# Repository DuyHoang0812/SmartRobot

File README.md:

# SmartRobot

SmartRobot là hệ thống quản lý và điều khiển xe robot ESP32 qua web. Người dùng có thể xem trạng thái xe, nhận quyền điều khiển, lái bằng bàn phím hoặc D-Pad và chuyển sang chế độ tự tránh vật cản. Quản trị viên quản lý tài khoản, xe và thông tin xác thực của từng thiết bị.

Hệ thống gồm frontend React, backend FastAPI, PostgreSQL và firmware ESP-IDF. ESP32 kết nối Wi-Fi và chủ động trao đổi với backend qua HTTP(S); trình duyệt nhận trạng thái qua REST và WebSocket. Mỗi xe có thông tin xác thực riêng, hỗ trợ nhiều xe cùng hoạt động.

## Mục lục

- [Chức năng](#chức-năng)
- [Kiến trúc dự án](#kiến-trúc-dự-án)
- [Nguyên lý hoạt động](#nguyên-lý-hoạt-động)
- [Phần cứng và sơ đồ chân](#phần-cứng-và-sơ-đồ-chân)
- [Setup và chạy web](#setup-và-chạy-web)
- [Setup, build và nạp firmware](#setup-build-và-nạp-firmware)
- [Chạy toàn bộ hệ thống](#chạy-toàn-bộ-hệ-thống)
- [Kiểm thử và kiểm tra bản build](#kiểm-thử-và-kiểm-tra-bản-build)
- [Xử lý lỗi thường gặp](#xử-lý-lỗi-thường-gặp)
- [Tài liệu chi tiết](#tài-liệu-chi-tiết)

## Chức năng

| Đối tượng | Chức năng |
| --- | --- |
| Người dùng | Đăng nhập, xem danh sách và chi tiết xe, tìm/lọc xe Online–Offline–Busy |
| Người điều khiển | Nhận/Trả xe, điều khiển Tiến/Lùi/Trái/Phải, chọn Manual/Auto, theo dõi cảm biến và xác nhận lệnh |
| Quản trị viên | Tạo/sửa tài khoản, đổi quyền, kích hoạt/vô hiệu hóa, đặt lại mật khẩu; quản lý xe và xoay credential |
| ESP32 | Xác thực, heartbeat, lấy lệnh, gửi ACK và telemetry, điều khiển motor/servo/còi/relay, giám sát điều kiện dừng cục bộ |

Không có tài khoản mặc định hay đăng ký công khai. Admin đầu tiên được tạo bằng CLI; các tài khoản tiếp theo được tạo trên trang quản trị.

## Kiến trúc dự án

```mermaid
flowchart LR
    User[Người dùng] --> Web[React / Vite]
    Web -->|REST: đăng nhập, quản lý, điều khiển| API[FastAPI]
    API -->|WebSocket: trạng thái xe| Web
    API <-->|SQLAlchemy / psycopg| DB[(PostgreSQL)]
    ESP[ESP32 / ESP-IDF] -->|HTTP client: auth, heartbeat, poll, ACK, telemetry| API
    ESP --> Motor[L298N / Động cơ]
    ESP <-->|Đo khoảng cách| Sensor[HC-SR04]
    ESP --> Outputs[Servo / Buzzer / Relay]
```

Backend lưu quyền điều khiển, lệnh và trạng thái thiết bị trong PostgreSQL. ESP32 chủ động poll lệnh nên backend không cần biết IP của xe và xe không cần chạy web server. WebSocket phục vụ cập nhật giao diện; đường truyền lệnh tới xe đi qua Device API.

| Thành phần | Công nghệ và trách nhiệm |
| --- | --- |
| Frontend | React 19, TypeScript, Vite, Tailwind CSS, TanStack Query, React Router; giao diện, phiên đăng nhập, REST và WebSocket |
| Backend | Python 3.12+, FastAPI, SQLAlchemy, Alembic; phân quyền, quản lý xe, điều phối lệnh và Device API |
| Database | PostgreSQL 18; người dùng, phiên đăng nhập, xe, lượt mượn, lệnh, telemetry và audit log |
| Firmware | C, ESP-IDF qua PlatformIO; tác vụ FreeRTOS cho giao tiếp, cảm biến, điều khiển và watchdog |

```text
SmartRobot/
├── README.md                 # Hướng dẫn chung
├── .env.example              # Mẫu cấu hình backend và PostgreSQL
├── .env.test.example         # Mẫu cấu hình database kiểm thử
├── compose.yaml              # PostgreSQL cho môi trường local
├── backend/
│   ├── app/api/              # REST endpoints và dependencies xác thực
│   ├── app/core/             # Settings, bảo mật, xử lý lỗi
│   ├── app/models/           # Models SQLAlchemy
│   ├── app/schemas/          # Request/response schemas
│   ├── app/services/         # Nghiệp vụ, điều khiển và Device API
│   ├── app/repositories/     # Truy cập dữ liệu
│   ├── app/websocket/        # Luồng trạng thái realtime
│   ├── migrations/          # Alembic migrations
│   ├── scripts/             # Tạo admin, chuẩn bị database test
│   └── tests/               # Kiểm thử backend
├── frontend/
│   ├── src/pages/           # Dashboard, điều khiển, quản trị, đăng nhập
│   ├── src/components/      # Thành phần giao diện
│   ├── src/hooks/           # Polling, xác thực, vòng đời điều khiển
│   ├── src/services/        # HTTP client và WebSocket
│   └── src/test/            # Kiểm thử frontend
├── firmware/
│   ├── platformio.ini       # Target ESP32 và framework ESP-IDF
│   ├── device.example.json  # Mẫu cấu hình riêng cho từng xe
│   ├── partitions.csv       # Flash layout, gồm partition robot_cfg
│   ├── src/                 # Firmware đang được build
│   ├── tools/               # Provision NVS, kiểm tra board và giao thức
│   ├── test/                # Kiểm thử trên host
│   └── ver2_6_esp32.ino      # Bản Arduino tham chiếu thuật toán
├── docs/                    # Giao thức, báo cáo và lịch sử sửa lỗi
└── schematic/               # Thư mục dành cho tài liệu mạch
```

Firmware hiện tại được build từ `firmware/src/` bằng ESP-IDF. File `.ino` là bản tham chiếu, không phải entry point của bản build này.

## Nguyên lý hoạt động

### Đăng nhập và quyền truy cập

Backend kiểm tra mật khẩu bằng Argon2id, cấp access JWT ngắn hạn và refresh token qua cookie HttpOnly. Frontend giữ access token trong bộ nhớ, tự refresh phiên và gửi CSRF token khi cần. Role `USER` sử dụng dashboard/điều khiển; `ADMIN` có thêm quyền quản trị.

Mỗi ESP32 dùng `device_id` và `device_secret` riêng, không dùng JWT của người dùng. Device API nhận các header `X-Device-ID`, `X-Device-Secret` và `X-Device-Session` sau khi xác thực. Xoay credential hoặc vô hiệu hóa xe sẽ thu hồi phiên thiết bị và quyền điều khiển liên quan.

### Từ khởi động xe đến thực thi lệnh

1. ESP32 khởi tạo đầu ra ở trạng thái dừng, đọc cấu hình từ partition NVS `robot_cfg`, kết nối Wi-Fi và xác thực với backend bằng boot UUID.
2. Thiết bị gửi heartbeat mặc định mỗi 2 giây, poll lệnh mỗi 100 ms và gửi telemetry tối đa 5 Hz. Chỉ heartbeat hợp lệ cập nhật trạng thái Online; sau 15 giây không có heartbeat, xe chuyển Offline.
3. Người dùng chọn **Nhận điều khiển**. Backend cấp một lượt mượn độc quyền cho xe và yêu cầu chuyển về Manual an toàn trước khi mở điều khiển.
4. Web gửi lệnh kèm thông tin lượt mượn, UUID chống lặp và sequence. Backend kiểm tra quyền rồi công bố lệnh có thời hạn cho thiết bị.
5. ESP32 kiểm tra phiên, sequence/generation, thời hạn và điều kiện cảm biến trước khi áp dụng; sau đó gửi ACK và telemetry. Backend đưa trạng thái đã nhận về web qua WebSocket.
6. **Trả xe** dừng chuyển động và đóng lượt mượn. Tắt/vô hiệu hóa tài khoản hoặc xe cũng thu hồi quyền tương ứng.

Một xe chỉ có một lượt mượn đang hoạt động. Lượt mượn giữ đến khi trả xe; `CONTROL_LEASE_SECONDS` còn trong cấu hình để tương thích, không phải hạn tự trả xe. Reload hoặc đăng nhập lại cùng tài khoản có thể nhận lại quyền bằng secret mới. Logout dừng lệnh nhưng giữ lượt mượn.

`Online` nghĩa là heartbeat còn mới; `Busy` nghĩa là xe Online và có lượt mượn hợp lệ. ACK `APPLIED` thể hiện firmware đã chấp nhận áp dụng lệnh. Telemetry chuyển động phản ánh đầu ra điện của driver; xe chưa có encoder để xác nhận vận tốc hoặc bánh đã quay.

### Manual, Auto và cơ chế dừng

**Manual:** giữ D-Pad, WASD hoặc phím mũi tên để gửi lệnh khoảng 4 lần/giây; nhả nút gửi STOP. TTL mặc định của lệnh Manual là 700 ms. Tiến cần dữ liệu cảm biến mới, hợp lệ, hướng giữa; dưới 15 cm sẽ dừng và bật còi. Lùi/quay Manual cần bật `allow_blind_manual`, giới hạn từng đợt mặc định 300 ms vì xe không có cảm biến sau/bên.

**Auto:** chỉ chạy sau khi chuyển chế độ đã được thiết bị xác nhận và permit còn hạn. Thuật toán hiện tại theo bản `ver2_6`:

- Khoảng cách phía trước từ 40 cm: tiến với `full_speed`; từ 15 đến dưới 40 cm: tiến với `slow_speed`.
- Dưới 15 cm: dừng, nhìn trái trước; nếu trái không đủ trống/chưa rõ thì nhìn phải. Servo đặt góc 0°/90°/180° và chờ ổn định 600 ms trước khi lấy số đo.
- Có hướng trống: về giữa lấy mẫu hợp lệ, lùi mặc định 400 ms, hãm 100 ms, quay mặc định 400 ms, hãm 100 ms rồi đo lại.
- Hai bên bị chắn: về giữa và kiểm tra lại. Khoảng cách thay đổi không quá 5 cm trong 3 giây khi đang tiến kích hoạt nhánh lùi/quay trái; đây là heuristic khoảng cách.

Control tick mục tiêu 10 ms và watchdog 20 ms chạy tách khỏi HTTP. Lệnh/permit hết hạn, mất liên lạc kéo dài hoặc lỗi cảm biến/driver sẽ chặn chuyển động. Không có echo hoặc số đo lỗi được báo là lỗi cảm biến, không coi là đường trống. Mất focus, ẩn tab, mất WebSocket hoặc rời trang cũng khiến frontend ngừng gửi chuyển động và cố gắng STOP.

Relay active-low cấp nguồn motor: giữ ON khi thiết bị xác nhận lượt mượn hợp lệ, kể cả Manual đứng yên hoặc STOP; chỉ PWM dừng. Trả xe hoặc watchdog/lỗi nghiêm trọng tắt relay. Firmware chờ nguồn ổn định 50 ms trước PWM. Các chu kỳ phần mềm trên không thay thế phép đo thời gian dừng trên xe thật.

## Phần cứng và sơ đồ chân

Target là ESP32 DevKit (`esp32dev`), flash 4 MB, driver L298N, cảm biến HC-SR04 trên servo, buzzer và relay cấp nguồn motor.

| Thiết bị | GPIO / cấu hình |
| --- | --- |
| L298N IN1 / IN2, bánh phải OUT1/OUT2 | 19 / 21 |
| L298N IN3 / IN4, bánh trái OUT3/OUT4 | 5 / 18 |
| HC-SR04 TRIG / ECHO | 27 / 14 |
| Servo | 13; 50 Hz, 500–2400 µs; trái 0°, giữa 90°, phải 180° |
| Buzzer active-high | 12 |
| Relay active-low | 26; HIGH = OFF |

PWM motor đặt trên IN1–IN4, 1 kHz, độ phân giải 8 bit. Không có GPIO ENA/ENB trong firmware; các chân enable phải được đấu/jumper đúng trên mạch. Duty mặc định `full/slow/turn = 75/30/75` trên thang 0–255, không phải phần trăm.

ECHO HC-SR04 cần chia áp/level shifting về 3,3 V. Đảm bảo chung GND, nguồn motor/servo phù hợp và tải relay đúng định mức. GPIO5/GPIO12 liên quan boot strapping nên cần kiểm tra mức điện lúc reset. Ngắt nguồn motor khi đấu dây/nạp lần đầu và kê bánh trước khi thử điều khiển.

## Setup và chạy web

### 1. Chuẩn bị môi trường

- Python 3.12 trở lên và `uv`.
- Node.js 22.13+ thuộc dòng 22 hoặc Node.js 24+, kèm npm; Node.js 24 đáp ứng bộ công cụ đã khóa trong repository.
- Docker và Docker Compose.
- Khi dùng xe thật: PlatformIO Core (`pio`), cáp USB dữ liệu, quyền truy cập cổng serial và Wi-Fi 2,4 GHz mà ESP32 hỗ trợ.

Các lệnh dưới đây giả định terminal đang ở thư mục gốc repository, trừ khi có bước `cd`. Với môi trường đã có cấu hình, giữ nguyên file local; chỉ sao chép mẫu cho lần setup mới.

### 2. Tạo cấu hình backend và database

```bash
cp .env.example .env
```

Điền các giá trị sau trong `.env`:

| Biến | Cách cấu hình |
| --- | --- |
| `POSTGRES_PASSWORD` | Mật khẩu PostgreSQL tự đặt |
| `DATABASE_URL` | `postgresql+psycopg://smartrobot:<mật-khẩu-URL-encoded>@127.0.0.1:5432/smartrobot` |
| `JWT_SECRET` | Chuỗi ngẫu nhiên riêng, ít nhất 32 bytes |
| `CORS_ORIGINS` | Mặc định cho `http://127.0.0.1:5173` và `http://localhost:5173` |
| `DEVICE_ALLOW_INSECURE_HTTP` | Giữ `false` cho HTTPS; đặt `true` khi thử ESP32 qua HTTP trong LAN riêng |

Có thể sinh JWT secret bằng `python3 -c 'import secrets; print(secrets.token_urlsafe(64))'`, rồi lưu vào `.env`. Không commit `.env`, `.env.test` hoặc credential thiết bị. Mật khẩu trong `DATABASE_URL` phải tương ứng với `POSTGRES_PASSWORD` và được URL-encode nếu có ký tự đặc biệt.

```bash
docker compose up -d postgres
docker compose ps
cd backend
uv sync --locked
uv run alembic upgrade head
uv run python -m scripts.create_admin
```

Chờ PostgreSQL healthy trước khi chạy migration. CLI tạo Admin hỏi username, email và mật khẩu 12–128 ký tự bằng nhập ẩn; không có mật khẩu mặc định. CLI từ chối tạo thêm khi đã có Admin hoạt động.

Migration hiện tại là `0005_persistent_borrow`; ứng dụng không tự tạo bảng lúc khởi động. Khi cập nhật source, chạy lại `alembic upgrade head`; không xóa Docker volume để cập nhật schema.

### 3. Chạy backend

Từ `backend/`:

```bash
uv run uvicorn app.main:app --reload --host 127.0.0.1 --port 8000 --no-proxy-headers
```

| Địa chỉ | Mục đích |
| --- | --- |
| `http://127.0.0.1:8000/docs` | Swagger/OpenAPI |
| `http://127.0.0.1:8000/api/v1/health` | Liveness |
| `http://127.0.0.1:8000/api/v1/health/ready` | Kiểm tra kết nối database |

### 4. Chạy frontend

Mở terminal khác, từ gốc repository:

```bash
cd frontend
npm ci
npm run dev
```

Mở **http://127.0.0.1:5173/login** và đăng nhập bằng Admin vừa tạo. Vite proxy `/api` và WebSocket tới backend `127.0.0.1:8000`; frontend không cần file cấu hình API URL hoặc secret riêng.

Các trang chính: `/dashboard`, `/robots/:id`, `/admin/users`, `/admin/robots`. Tạo xe tại trang quản trị và lưu `Device ID` cùng `Device Secret` để cấu hình firmware. Secret chỉ hiện một lần; nếu mất, xoay credential và cập nhật lại NVS cho xe.

### 5. Cho ESP32 truy cập backend trong LAN

ESP32 không truy cập được backend chỉ bind `127.0.0.1`. Khi thử HTTP trong LAN riêng, đặt `DEVICE_ALLOW_INSECURE_HTTP=true` trong `.env`, dừng tiến trình backend cũ và chạy từ `backend/`:

```bash
uv run uvicorn app.main:app --reload --host 0.0.0.0 --port 8000 --no-proxy-headers
```

Trong cấu hình firmware, dùng ví dụ `http://192.168.1.10:8000/api/v1/devices`, thay IP bằng IPv4 LAN của máy chạy backend, đồng thời bật `allow_http_lan=true`. Cho phép cổng 8000 từ LAN qua firewall và kiểm tra Wi-Fi không chặn liên lạc giữa các thiết bị. Không dùng `localhost` hoặc `0.0.0.0` làm địa chỉ đích của ESP32.

HTTP truyền credential không mã hóa, chỉ dùng cho LAN phát triển. Khi triển khai, dùng HTTPS; xem cấu hình bên dưới.

### 6. Build web và triển khai

```bash
cd frontend
npm run build
```

Output ở `frontend/dist/`. Phục vụ thư mục này bằng web server/reverse proxy, cấu hình fallback về `index.html` cho React Router, chuyển tiếp `/api` tới FastAPI và hỗ trợ WebSocket Upgrade. Frontend và API cần cùng origin HTTPS; Vite dev proxy không được đóng gói vào bản build. `npm run preview` chỉ xem thử bản build frontend, cần cấu hình API riêng nếu muốn chạy cả hệ thống.

Backend production chạy không có `--reload`, với `.env` có `ENVIRONMENT=production`, `COOKIE_SECURE=true`, `JWT_SECRET` hợp lệ, `CORS_ORIGINS` là origin HTTPS cụ thể và `DEVICE_ALLOW_INSECURE_HTTP=false`. Khi kết thúc TLS tại reverse proxy, cấu hình Uvicorn chỉ tin proxy headers từ IP proxy được chỉ định để Device API nhận đúng scheme HTTPS.

## Setup, build và nạp firmware

### 1. Build firmware ESP-IDF

Từ gốc repository:

```bash
cd firmware
pio run
```

PlatformIO tải platform `espressif32@7.1.1`, toolchain và ESP-IDF 6.1.0. Dependency cJSON được khóa trong `dependencies.lock`. Lần build đầu cần Internet và dung lượng để tải toolchain. Firmware nhắm flash 4 MB, app partition 3 MB; bản hiện tại không có OTA.

### 2. Cấu hình riêng cho xe

Từ `firmware/`, tạo file local:

```bash
umask 077
cp device.example.json device.local.json
chmod 600 device.local.json
```

Điền bằng editor:

| Trường | Giá trị / ý nghĩa |
| --- | --- |
| `wifi_ssid`, `wifi_password` | Wi-Fi của xe; password rỗng cho mạng mở, nếu có phải ít nhất 8 bytes |
| `backend_url` | URL kết thúc chính xác `/api/v1/devices`, không dấu `/` cuối, query hoặc thông tin đăng nhập |
| `device_id`, `device_secret` | Thông tin do Admin cấp cho đúng xe |
| `ca_file` | File CA PEM tương đối với JSON, tối đa 3900 bytes; rỗng dùng bundle CA công khai |
| `ntp_server` | Mặc định `pool.ntp.org`; HTTPS cần đồng bộ giờ trước khi xác thực |
| `allow_http_lan` | Mặc định `false`; HTTP thử nghiệm cần `true` ở đây và backend; chỉ chấp nhận IPv4 LAN dạng số |
| `motors_enabled` | Mặc định `false`; bật `true` sau kiểm tra dây và kê bánh để cho phép motor hoạt động |
| `allow_blind_manual` | Mặc định `false`; bật nếu muốn thử Lùi/Trái/Phải Manual sau khi kiểm tra không gian xung quanh |
| `blind_manual_max_ms` | Mặc định 300 ms, khoảng 50–400 ms; giữ nút không kéo dài đợt mù, cần nhả/STOP để mở đợt mới |
| `full_speed`, `slow_speed`, `turn_speed` | Mặc định 75/30/75, khoảng 1–255; `slow_speed <= full_speed` |
| `left_motor_percent`, `right_motor_percent` | Bù PWM mỗi bánh, mặc định 100/83.5; khoảng 50–150, tối đa một số lẻ |
| `auto_backup_ms` | Thời gian lùi Auto, mặc định 400 ms, khoảng 50–400 ms |
| `auto_turn_left_ms`, `auto_turn_right_ms` | Thời gian quay Auto, mặc định 400/400 ms, khoảng 100–1200 ms |
| `auto_clearance_cm` | Trường cấu hình tương thích, mặc định 15; thuật toán Auto hiện tại xét khoảng trống bằng ngưỡng 15 cm trong code |
| `http_timeout_ms` | Giá trị tương thích mặc định 250; runtime áp dụng sàn timeout request 400 ms, không kéo dài TTL lệnh |
| `relay_console` | Key tương thích; nguồn motor do luồng điều khiển quản lý tự động |

Ví dụ LAN: `backend_url` là `http://192.168.1.10:8000/api/v1/devices` và `allow_http_lan=true`. HTTPS phải có hostname/IP khớp chứng chỉ; dùng `ca_file` nếu CA nội bộ. Không bỏ kiểm tra chứng chỉ để xử lý lỗi kết nối hoặc sai giờ.

### 3. Tạo image cấu hình NVS

Sau `pio run`, từ `firmware/`:

```bash
IDF_PYTHON="$HOME/.platformio/penv/.espidf-6.1.0/bin/python"
"$IDF_PYTHON" -m pip install -r tools/requirements.txt
python3 tools/provision.py
```

Nếu PlatformIO dùng đường dẫn khác, đặt `PLATFORMIO_CORE_DIR` hoặc truyền `--idf-python <đường-dẫn-python-ESP-IDF>` cho `provision.py`. Script chỉ sinh `secrets/robot_cfg.bin` kích thước 64 KB, quyền 0600, không flash hoặc mở serial và không in secret.

Wi-Fi và Device Secret không nằm trong app image. `device.local.json`, `secrets/`, managed dependencies và build cache đã được gitignore. NVS cấu hình hiện chưa mã hóa trên flash.

### 4. Nạp app và cấu hình

Ngắt nguồn motor/tải relay trước lần nạp đầu, chọn đúng cổng serial. Từ `firmware/`:

```bash
pio run -t upload --upload-port /dev/ttyUSB0
pio pkg exec -p tool-esptoolpy -- esptool.py --chip esp32 \
  --port /dev/ttyUSB0 --baud 115200 write_flash 0x310000 secrets/robot_cfg.bin
pio device monitor --port /dev/ttyUSB0 --baud 115200
```

Thay `/dev/ttyUSB0` bằng cổng thực tế, chẳng hạn `/dev/ttyACM0` hoặc `COM3`. Reset sau khi nạp cấu hình. Partition `robot_cfg` nằm ở `0x310000`, kích thước `0x10000`; upload app thông thường không ghi đè partition này. Khi đổi Wi-Fi, backend URL hoặc xoay Device Secret, sửa JSON, tạo lại image NVS rồi nạp lại partition cấu hình. Không cần erase toàn bộ flash.

Thiếu hoặc sai cấu hình khiến startup giữ motor/relay OFF. Xem log khởi động, kết nối Wi-Fi và xác thực thiết bị trước khi cấp nguồn motor để thử xe.

### 5. Kiểm tra và hiệu chỉnh qua Serial

| Lệnh | Tác dụng |
| --- | --- |
| `status` | Xem mode, output, sensor, relay, PWM, trim, sequence và deadline |
| `trim 100 83.5` | Áp dụng bù PWM trái/phải; cần Manual và xe dừng |
| `trim save` | Lưu trim vào NVS |
| `auto reference` | Áp dụng bộ Auto tham chiếu 15 cm / lùi 400 ms / quay 400 ms; cần Manual và xe dừng |
| `auto save` | Lưu bộ thông số Auto vào NVS |
| `relay off` | Tắt nguồn motor và hủy intent hiện tại |

`relay on` và `relay toggle` bị từ chối vì relay được quản lý theo quyền điều khiển. Trim mặc định là điểm bắt đầu; cần cân lại trên xe thực tế. Chọn Manual, nhả hết nút trước khi đổi/lưu thông số.

## Chạy toàn bộ hệ thống

1. Khởi động PostgreSQL, chạy migration, mở backend và frontend.
2. Đăng nhập Admin, tạo tài khoản người dùng và xe; lấy credential riêng cho ESP32.
3. Build, cấp cấu hình và nạp firmware. Với HTTP LAN, kiểm tra backend bind `0.0.0.0`, URL đúng IP máy chủ và cả hai phía đều bật HTTP development.
4. Mở Serial monitor, chờ xác thực thành công và heartbeat; dashboard phải chuyển xe sang Online.
5. Mở xe, chọn **Nhận điều khiển**, chờ thiết bị xác nhận Manual. Nếu chuẩn bị thử motor, phải có `motors_enabled=true` trong cấu hình đã nạp.
6. Thử Tiến ở vùng trống rồi nhả nút; thử Lùi/Trái/Phải nếu đã bật `allow_blind_manual`. Đối chiếu Serial, ACK và telemetry trên web.
7. Chuyển Auto và thử vật cản có kiểm soát; kiểm tra chuyển lại Manual, mất kết nối và **Trả xe**. Trả xe phải dừng PWM và tắt relay.

Một terminal chạy backend, một terminal chạy frontend và một terminal tùy chọn cho Serial monitor. Khi dừng môi trường local, dùng `Ctrl+C` cho các tiến trình và `docker compose stop postgres` ở gốc repository để giữ dữ liệu.

## Kiểm thử và kiểm tra bản build

### Backend

Các kiểm thử có database cần PostgreSQL riêng, tên kết thúc `_test`, khác database phát triển. Từ `backend/`, nếu chưa có `.env.test`:

```bash
uv run python -m scripts.prepare_test_database
```

Script tạo database `smartrobot_test` và `.env.test`, yêu cầu role PostgreSQL có quyền `CREATEDB`. Nếu đã có `.env.test`, giữ cấu hình hiện tại; nếu provision thủ công, dùng `.env.test.example` làm mẫu và tạo database riêng trước.

```bash
uv run pytest
uv run ruff check app tests scripts migrations
uv run ruff format --check app tests scripts migrations
uv run alembic check
```

`alembic check` cần database đã được migrate tới head.

### Frontend

Từ `frontend/`, sau `npm ci`:

```bash
npm run lint
npm run test
npm run build
```

### Firmware

Từ gốc repository, sau `pio run` trong `firmware/` để tải managed cJSON; kiểm thử host cần C compiler:

```bash
python3 -m unittest discover -s firmware/test -p 'test_*.py' -v
python3 firmware/tools/check_board.py
mkdir -p firmware/.pio/host
cc -std=c11 -Wall -Wextra -Werror -fsanitize=address,undefined -g \
  -I firmware/src -I firmware/managed_components/espressif__cjson/cJSON \
  firmware/src/protocol.c firmware/src/telemetry.c \
  firmware/managed_components/espressif__cjson/cJSON/cJSON.c \
  firmware/test/protocol_test.c -lm -o firmware/.pio/host/protocol_test
ASAN_OPTIONS=detect_leaks=0 firmware/.pio/host/protocol_test
ASAN_OPTIONS=detect_leaks=0 backend/.venv/bin/python firmware/tools/check_contract.py
```

Kiểm thử host xác minh logic và giao thức bằng môi trường giả lập API phần cứng, không thay thế kiểm tra dây, chiều bánh, nguồn và thời gian phản ứng trên xe thật.

## Xử lý lỗi thường gặp

| Hiện tượng | Kiểm tra |
| --- | --- |
| Backend không kết nối được PostgreSQL | Container healthy, cổng 5432, mật khẩu trong URL, URL-encoding và migration |
| Login trả 503 | `JWT_SECRET` đã được điền và backend đã khởi động lại |
| Login/refresh bị từ chối Origin hoặc CSRF | Dùng origin đúng `CORS_ORIGINS`; frontend đi qua proxy `/api`; HTTP client thủ công phải gửi Origin/CSRF theo API |
| Xe luôn Offline | Nguồn/Wi-Fi, backend bind LAN, IP/port/firewall, credential, HTTP opt-in hoặc CA/NTP cho HTTPS; xem Serial |
| Device API trả 401/409 | Kiểm tra credential/session; nếu đã rotate secret cần cấp lại NVS và reset |
| Nhận điều khiển nhưng D-Pad khóa | Chờ xác nhận Manual an toàn, kiểm tra WebSocket, kết nối thiết bị và lượt mượn |
| Có ACK nhưng motor không chạy | `motors_enabled`, relay, nguồn motor, ENA/ENB, common GND, TTL lệnh và lỗi sensor; xem `status` |
| Lùi/quay Manual bị chặn hoặc dừng sau đợt ngắn | Kiểm tra `allow_blind_manual`, giới hạn burst; nhả nút rồi thử lại sau khi kiểm tra vùng trống |
| Khoảng cách null khi servo quay | Firmware chờ servo ổn định; nếu lỗi kéo dài, kiểm tra ECHO, chia áp, nguồn và dây cảm biến |
| WebSocket không nối khi triển khai | Reverse proxy cần Upgrade, đúng origin HTTPS/WSS và trusted proxy |
| Xe lệch hướng | Kiểm tra OUT1/2 = bánh phải, OUT3/4 = bánh trái; hiệu chỉnh trim và lưu NVS |

## Tài liệu chi tiết

- [Giao thức điều khiển](docs/robot-control-protocol.md): lease, sequence/generation, TTL và ACK.
- [ESP32 Device API](docs/esp32-device-api.md): xác thực, heartbeat, polling và telemetry.
- [Nền tảng backend](docs/backend-foundation.md): cấu trúc và database.
- [Báo cáo firmware](docs/phase-6b-report.md): kiểm thử và quy trình nghiệm thu.
- [Auto theo bản ver2_6](docs/fixes/auto-reference-web.md): thuật toán và thay đổi servo.
- [Relay theo lượt mượn](docs/fixes/borrow-powered-relay.md): quản lý nguồn motor.

Các báo cáo `docs/phase-*.md` và ghi chú trong `docs/fixes/` ghi lại từng thời điểm phát triển, có thể mô tả hành vi đã được thay thế. README này là hướng dẫn setup và vận hành tổng hợp cho source hiện tại.

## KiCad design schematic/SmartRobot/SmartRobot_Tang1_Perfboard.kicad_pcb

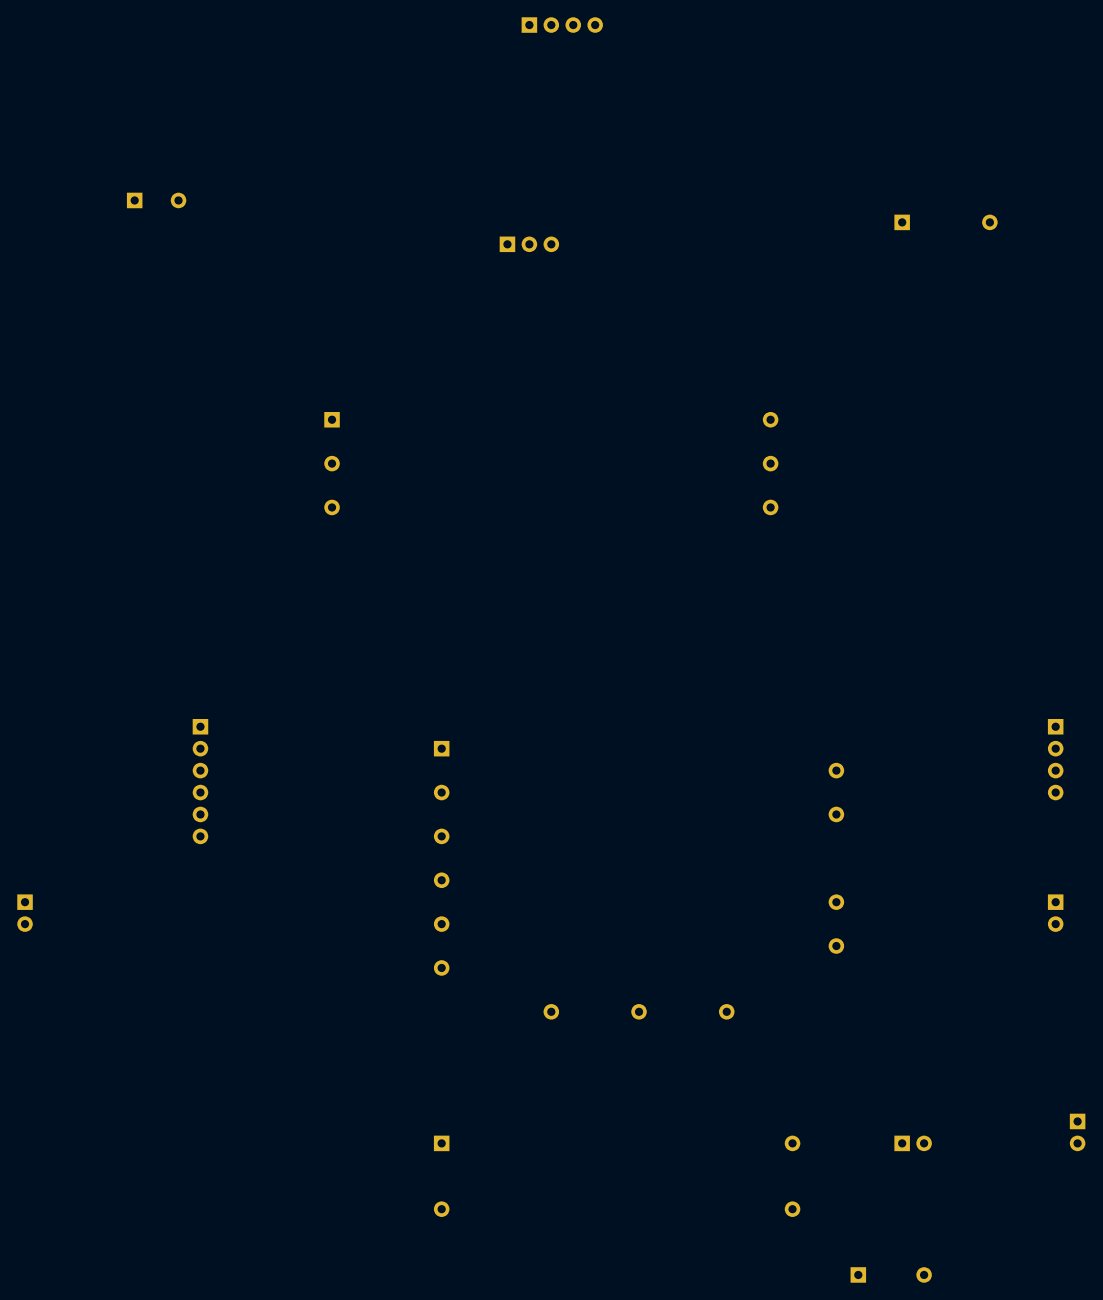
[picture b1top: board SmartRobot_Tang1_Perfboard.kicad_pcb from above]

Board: 2 copper layers, 14 parts (0 on the bottom side), 19 nets, no tracks yet.

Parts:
BZ1: BUZZER; Buzzer_2Pad
D1: LED RED; LED_D5_P2p54
J1: BATTERY INPUT FROM UPPER; Power_1x02_P2p54
J3: 4P LOWER <-> J2; PinHeader_1x04_P2p54
J5: 6P LOWER <-> J4; PinHeader_1x06_P2p54
M1, M2: DC MOTOR HARNESS; Motor_2Wire_Landing
M3: SG90 SERVO / FRONT; Servo_3Wire_Landing
R1: 1k; Resistor_7p62
SW1: POWER SWITCH - CHECK TYPE; Switch_2Wire_Landing
U2: BUCK 5V - VERIFY MODULE SIZE; Buck_4Wire_Landing
U3: L298N - MODULE TERMINAL LANDINGS; L298N_13Wire_Landing
U4: ULTRASONIC ABOVE SERVO; HC_SR04_4Wire_Landing
U5: RELAY 1CH - ASSUMED CONTACTS; Relay_Module_6Wire_Landing

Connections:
+5V_MOTOR_SW: U3.7 (VS), U5.5 (NO)
+5V_SYS: J5.1, M3.2 (+), R1.1, U2.3 (VOUT+), U3.9 (5V_LG), U4.1 (VCC), U5.1 (VCC), U5.4 (COM)
BAT_PROTECTED+: J1.1, SW1.1 (A)
BAT_SW: SW1.2 (B), U2.1 (VIN+)
BUZZER_CTRL: BZ1.1 (+), J5.6
GND: BZ1.2 (-), D1.1 (K), J1.2, M3.3 (-), U2.2 (VIN-), U2.4 (VOUT-), U3.8 (GND), U4.4 (GND), U5.2 (GND)
LED_R1_D1: D1.2 (A), R1.2
MOTOR_A_OUT1: M1.1 (+), U3.10 (OUT1)
MOTOR_A_OUT2: M1.2 (-), U3.11 (OUT2)
MOTOR_B_OUT3: M2.1 (+), U3.12 (OUT3)
MOTOR_B_OUT4: M2.2 (-), U3.13 (OUT4)
MOTOR_IN1: J3.1, U3.2 (IN1)
MOTOR_IN2: J3.2, U3.3 (IN2)
MOTOR_IN3: J3.3, U3.4 (IN3)
MOTOR_IN4: J3.4, U3.5 (IN4)
RELAY_IN: J5.5, U5.3 (IN)
SERVO_SIG: J5.4, M3.1 (PWM)
US_ECHO_RAW: J5.3, U4.3 (ECHO)
US_TRIG: J5.2, U4.2 (TRIG)

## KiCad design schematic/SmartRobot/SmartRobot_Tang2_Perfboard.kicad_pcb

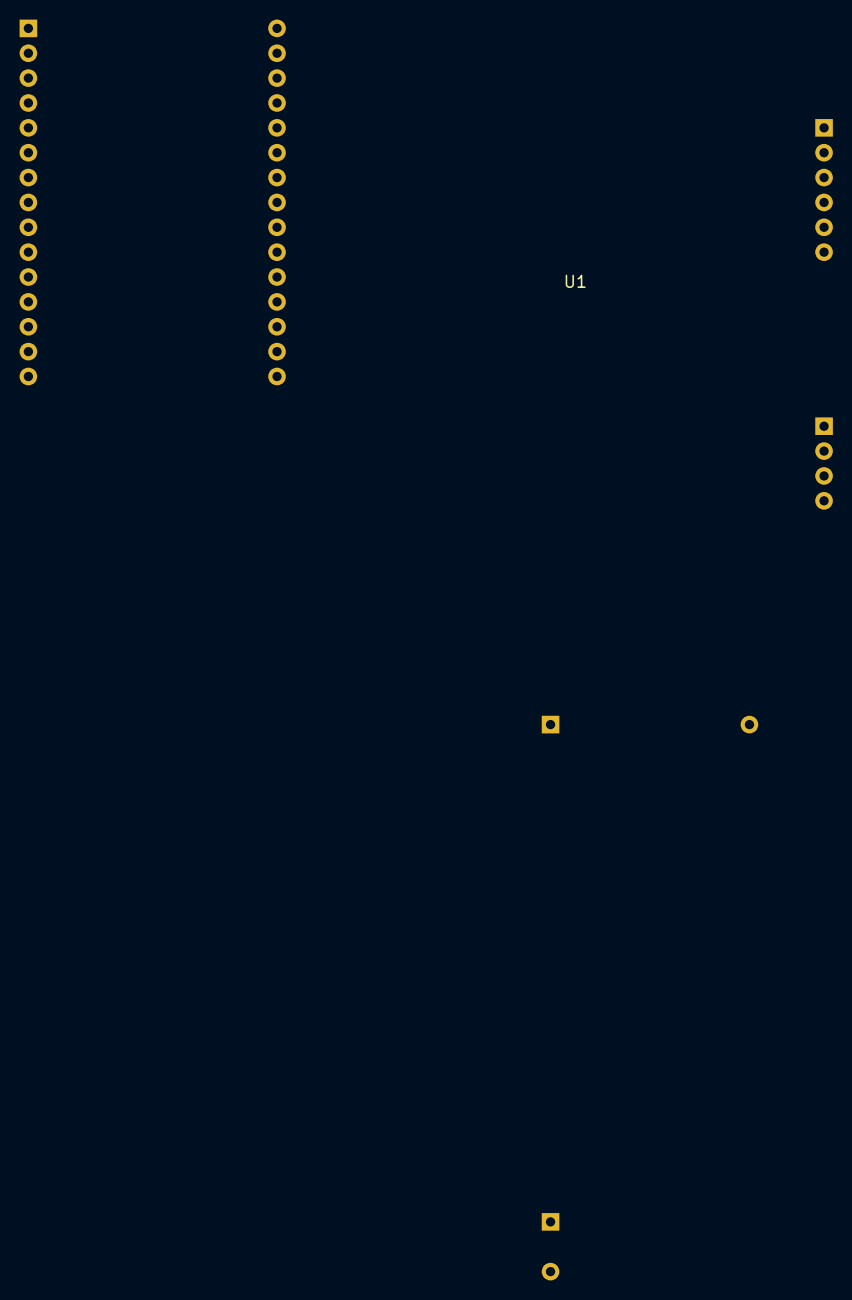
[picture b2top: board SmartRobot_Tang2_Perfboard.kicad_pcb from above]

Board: 2 copper layers, 5 parts (0 on the bottom side), 12 nets, no tracks yet.

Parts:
BT1: 3 x 18650 HOLDER / BATTERY LEADS; Battery_3x18650_Mechanical
J2: 4P - UPPER; PinHeader_1x04_P2p54
J4: 6P - UPPER; PinHeader_1x06_P2p54
R2: 10 Ohm / 2W (UNVERIFIED); Resistor_Axial_20p32
U1: ESP32 DEVKIT V1 30P - SOCKET; ESP32_30P_Pitch2p54_Rows25p4

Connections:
+5V_SYS: J4.1, R2.2
BUZZER_CTRL: J4.6, U1.12 (GPIO12)
GND: BT1.2 (-), U1.14 (GND), U1.17 (GND)
MOTOR_IN1: J2.1, U1.25 (GPIO19)
MOTOR_IN2: J2.2, U1.26 (GPIO21)
MOTOR_IN3: J2.3, U1.23 (GPIO5)
MOTOR_IN4: J2.4, U1.24 (GPIO18)
RELAY_IN: J4.5, U1.9 (GPIO26)
SERVO_SIG: J4.4, U1.13 (GPIO13)
US_ECHO_RAW: J4.3, U1.11 (GPIO14)
US_TRIG: J4.2, U1.10 (GPIO27)
VIN_AFTER_R2: R2.1, U1.15 (VIN)
